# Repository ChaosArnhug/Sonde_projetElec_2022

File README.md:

# Projet d'électonique 2022
Ce répo regroupe le code, les schémas Eagle et le Prothéus du projet d'électonique à l'Ephec en 2022 pour les 2ièmes années.

## Contexte 

* Les PIC’s deviennent avec le temps des composants universels des systèmes électroniques et des systèmes embarqués. Il semble donc opportun que les étudiants soient aptes à définir et développer une carte comportant non seulement un microcontrôleur PIC mais aussi les composants annexes minimaux nécessaires au bon fonctionnement de ce dernier

*  De manière à pouvoir ensuite tester et vérifier le bon fonctionnement de la carte PIC, il semble opportun de développer une application électronique se basant, au moinspour certaines de ses fonctions, sur le PIC

* Cette application sera un télémètre à ultrasons qui envoie auPIC la mesure d’une distance en cm

* La carte doit afficher la distance sur 2 afficheurs 7-segments

* La carte devra signaler une alerte lorsque la distance dépasse (ou tombe en dessous d’) un seuil critique défini par l’utilisateur

* Enfin, pour utiliser les connaissances du cours de Développement informatique II, le PIC devra communiquer avec une application PYTHON qui affichera la distance
mesurée et permettra de définir le seuil de déclenchement d’alerte

## Spécifications

* PIC : 18F458

* Sonde : HC-SR04

* Affichage distance : 2 7-segments à cathodes communes 

* Affichage alerte : LED rouge qui clignote

* Affichage aucune alerte : LED verte

* Gestion du seuil : interface codée en Python

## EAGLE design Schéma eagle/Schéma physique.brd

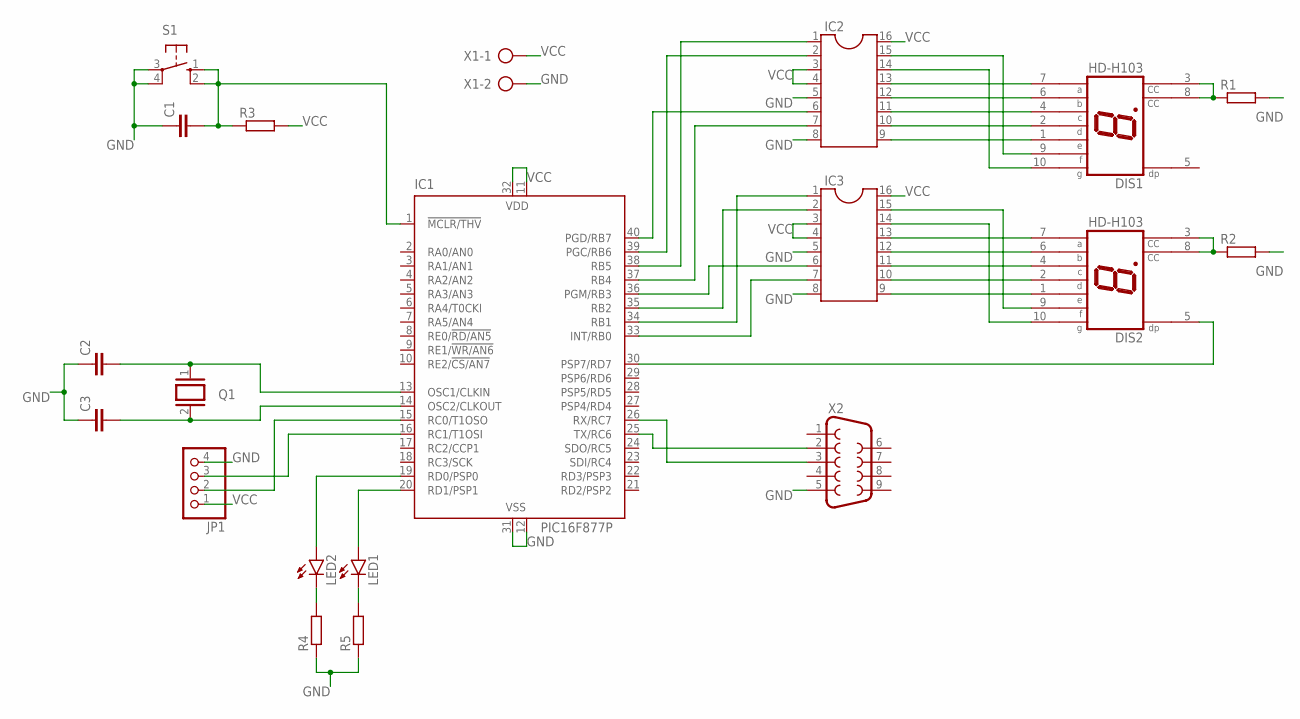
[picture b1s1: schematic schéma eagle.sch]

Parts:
C1, C2, C3: C-EU025-025X050; C025-025X050
DIS1, DIS2: HD-H103; HDSP-M
IC1: PIC16F877P; DIL40
IC2, IC3: DIL16
JP1: PINHD-1X4; 1X04
LED1, LED2: LED5MM
Q1: XTAL/S; QS
R1, R2, R3, R4, R5: R-EU_0207/10; 0207/10
S1: 10-XX; B3F-10XX
X1: AK300/2
X2: F09H

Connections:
GND: C1.1, C2.1, C3.1, IC1.12 (VSS), IC1.31 (VSS), IC2.5, IC2.8, IC3.5, IC3.8, JP1.4, R1.2, R2.2, R4.1, R5.1, S1.3, S1.4 (P1), X1.2, X2.5
unnamed: IC1.25 (TX/RC6), X2.2
unnamed: IC1.26 (RX/RC7), X2.3
unnamed: IC1.33 (INT/RB0), IC3.7
unnamed: IC1.34 (RB1), IC3.1
unnamed: IC1.35 (RB2), IC3.2
unnamed: IC1.36 (PGM/RB3), IC3.6
unnamed: IC1.37 (RB4), IC2.7
unnamed: IC1.38 (RB5), IC2.1
unnamed: IC1.39 (PGC/RB6), IC2.2
unnamed: IC1.40 (PGD/RB7), IC2.6
unnamed: DIS1.7 (A), IC2.13
unnamed: DIS1.6 (B), IC2.12
unnamed: DIS1.4 (C), IC2.11
unnamed: DIS1.2 (D), IC2.10
unnamed: DIS1.1 (E), IC2.9
unnamed: DIS1.9 (F), IC2.15
unnamed: DIS1.10 (G), IC2.14
unnamed: DIS2.7 (A), IC3.13
unnamed: DIS2.6 (B), IC3.12
unnamed: DIS2.4 (C), IC3.11
unnamed: DIS2.2 (D), IC3.10
unnamed: DIS2.1 (E), IC3.9
unnamed: DIS2.9 (F), IC3.15
unnamed: DIS2.10 (G), IC3.14
unnamed: DIS1.3 (CC), DIS1.8 (CC), R1.1
unnamed: DIS2.3 (CC), DIS2.8 (CC), R2.1
unnamed: DIS2.5 (DP), IC1.30 (PSP7/RD7)
unnamed: C1.2, IC1.1 (!MCLR/THV), R3.1, S1.1 (S), S1.2 (S1)
unnamed: C2.2, IC1.13 (OSC1/CLKIN), Q1.1
unnamed: C3.2, IC1.14 (OSC2/CLKOUT), Q1.2
unnamed: IC1.15 (RC0/T1OSO), JP1.2
unnamed: IC1.16 (RC1/T1OSI), JP1.3
unnamed: IC1.19 (RD0/PSP0), LED2.A
unnamed: IC1.20 (RD1/PSP1), LED1.A
unnamed: LED2.K (C), R4.2
unnamed: LED1.K (C), R5.2
VCC: IC1.11 (VDD), IC1.32 (VDD), IC2.3, IC2.4, IC2.16, IC3.3, IC3.4, IC3.16, JP1.1, R3.2, X1.1

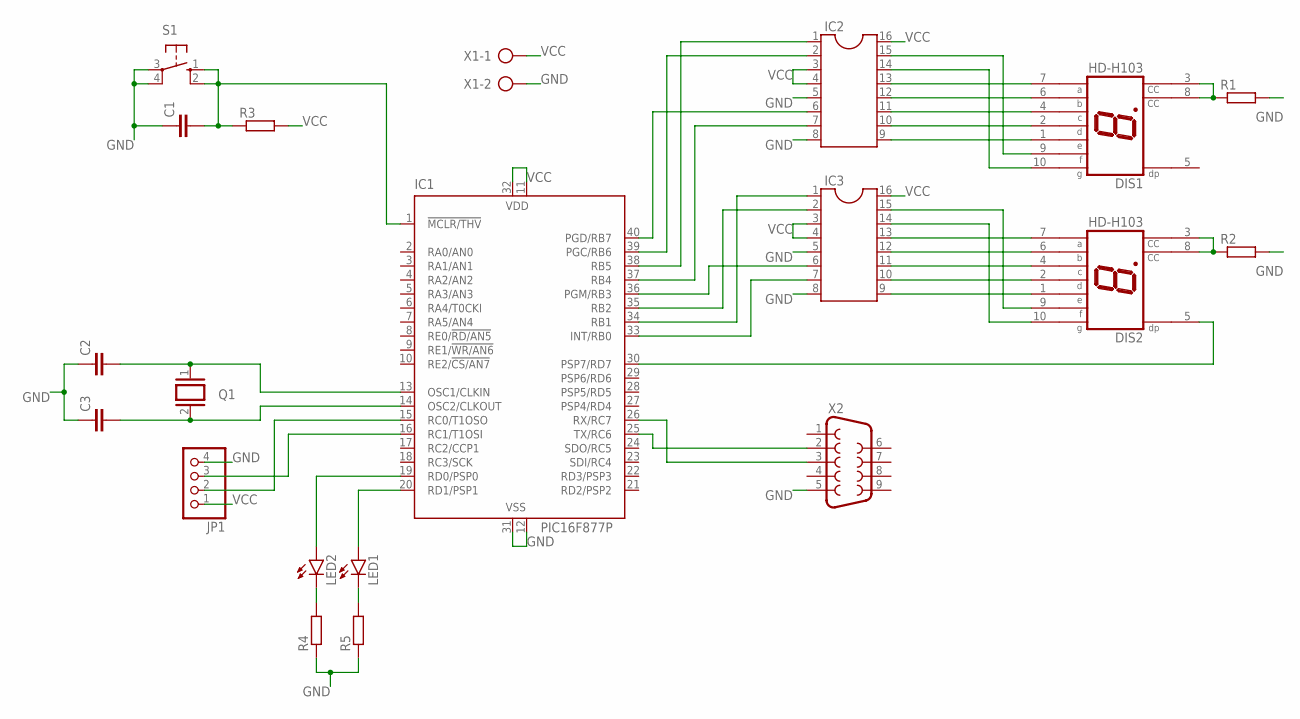
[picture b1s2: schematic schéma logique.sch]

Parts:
C1, C2, C3: C-EU025-025X050; C025-025X050
DIS1, DIS2: HD-H103; HDSP-M
IC1: PIC16F877P; DIL40
IC2, IC3: DIL16
JP1: PINHD-1X4; 1X04
LED1, LED2: LED5MM
Q1: XTAL/S; QS
R1, R2, R3, R4, R5: R-EU_0207/10; 0207/10
S1: 10-XX; B3F-10XX
X1: AK300/2
X2: F09H

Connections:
GND: C1.1, C2.1, C3.1, IC1.12 (VSS), IC1.31 (VSS), IC2.5, IC2.8, IC3.5, IC3.8, JP1.4, R1.2, R2.2, R4.1, R5.1, S1.3, S1.4 (P1), X1.2, X2.5
unnamed: IC1.25 (TX/RC6), X2.2
unnamed: IC1.26 (RX/RC7), X2.3
unnamed: IC1.33 (INT/RB0), IC3.7
unnamed: IC1.34 (RB1), IC3.1
unnamed: IC1.35 (RB2), IC3.2
unnamed: IC1.36 (PGM/RB3), IC3.6
unnamed: IC1.37 (RB4), IC2.7
unnamed: IC1.38 (RB5), IC2.1
unnamed: IC1.39 (PGC/RB6), IC2.2
unnamed: IC1.40 (PGD/RB7), IC2.6
unnamed: DIS1.7 (A), IC2.13
unnamed: DIS1.6 (B), IC2.12
unnamed: DIS1.4 (C), IC2.11
unnamed: DIS1.2 (D), IC2.10
unnamed: DIS1.1 (E), IC2.9
unnamed: DIS1.9 (F), IC2.15
unnamed: DIS1.10 (G), IC2.14
unnamed: DIS2.7 (A), IC3.13
unnamed: DIS2.6 (B), IC3.12
unnamed: DIS2.4 (C), IC3.11
unnamed: DIS2.2 (D), IC3.10
unnamed: DIS2.1 (E), IC3.9
unnamed: DIS2.9 (F), IC3.15
unnamed: DIS2.10 (G), IC3.14
unnamed: DIS1.3 (CC), DIS1.8 (CC), R1.1
unnamed: DIS2.3 (CC), DIS2.8 (CC), R2.1
unnamed: DIS2.5 (DP), IC1.30 (PSP7/RD7)
unnamed: C1.2, IC1.1 (!MCLR/THV), R3.1, S1.1 (S), S1.2 (S1)
unnamed: C2.2, IC1.13 (OSC1/CLKIN), Q1.1
unnamed: C3.2, IC1.14 (OSC2/CLKOUT), Q1.2
unnamed: IC1.15 (RC0/T1OSO), JP1.2
unnamed: IC1.16 (RC1/T1OSI), JP1.3
unnamed: IC1.19 (RD0/PSP0), LED2.A
unnamed: IC1.20 (RD1/PSP1), LED1.A
unnamed: LED2.K (C), R4.2
unnamed: LED1.K (C), R5.2
VCC: IC1.11 (VDD), IC1.32 (VDD), IC2.3, IC2.4, IC2.16, IC3.3, IC3.4, IC3.16, JP1.1, R3.2, X1.1

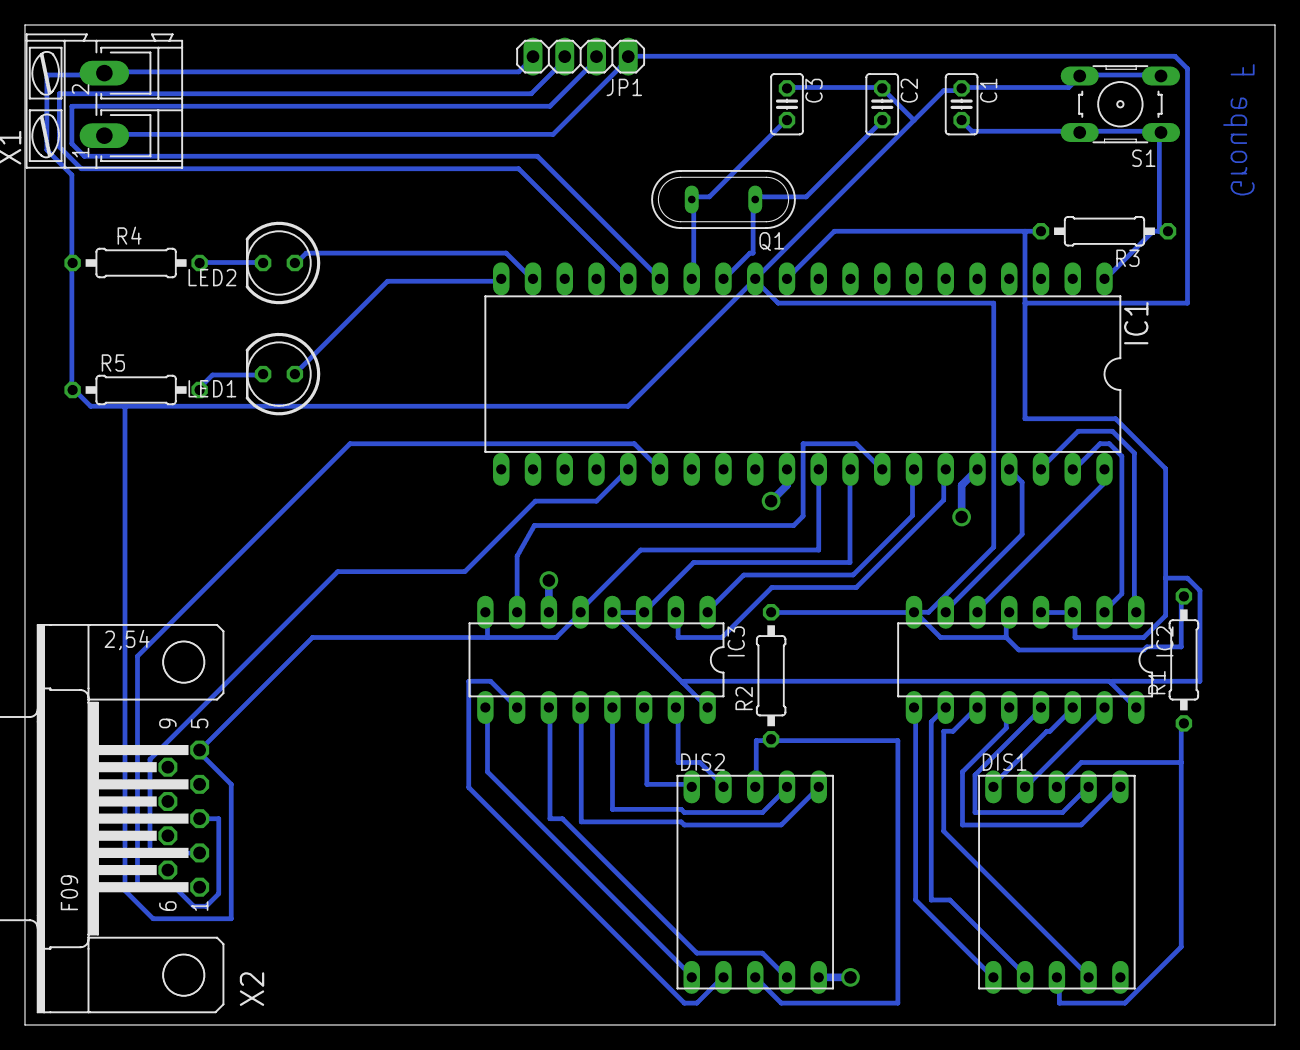
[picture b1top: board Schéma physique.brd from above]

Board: 2 copper layers, 100.0 x 80.0 mm, 20 parts (0 on the bottom side), 38 nets.

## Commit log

2022-04-26 [ADD] affichage 7 seg
    Pas encore débeugé mais tout le code/logique est là
2022-04-26 [FIX]correction code
2022-05-13 le main final on l'espère
2022-05-13 code final 2.0
    Changement du calcul du threshold.
2022-05-13 code final 2.1
    Plus besoin de la librairie stdlib.h
2022-05-16 Ajout du code
    Le code est entièrement fonctionnel sauf pour le problème de latence avec les données reçues pour l'alerte. (Temps record : 1"47"14)
2022-05-16 Rename Groupe F.brd to Schéma physique.brd
2022-05-16 Rename schéma eagle.sch to schéma logique.sch
2022-05-16 Rename main.c to code/main.c
2022-05-16 Rename main.h to code/main.h
2022-05-16 Rename main.py to code/main.py
2022-05-16 Version finale du "Hex" file
2022-05-16 Simulation Proteus
2022-05-16 Version Finale 2.0
